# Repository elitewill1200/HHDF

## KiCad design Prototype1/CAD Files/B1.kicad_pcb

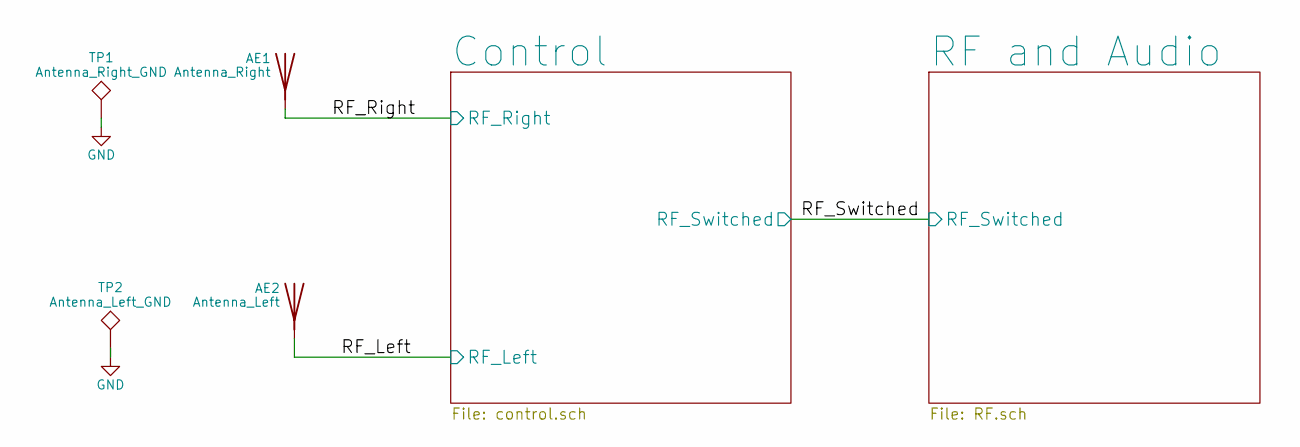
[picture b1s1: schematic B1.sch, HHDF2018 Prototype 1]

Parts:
AE1: Antenna_Right; MountingHole_5mm_Pad
AE2: Antenna_Left; MountingHole_5mm_Pad
TP1: Antenna_Right_GND; MountingHole_5mm_Pad
TP2: Antenna_Left_GND; MountingHole_5mm_Pad

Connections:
/RF_Left: AE2.1; also elsewhere on the board
/RF_Right: AE1.1; also elsewhere on the board
GND: TP1.1, TP2.1; also elsewhere on the board

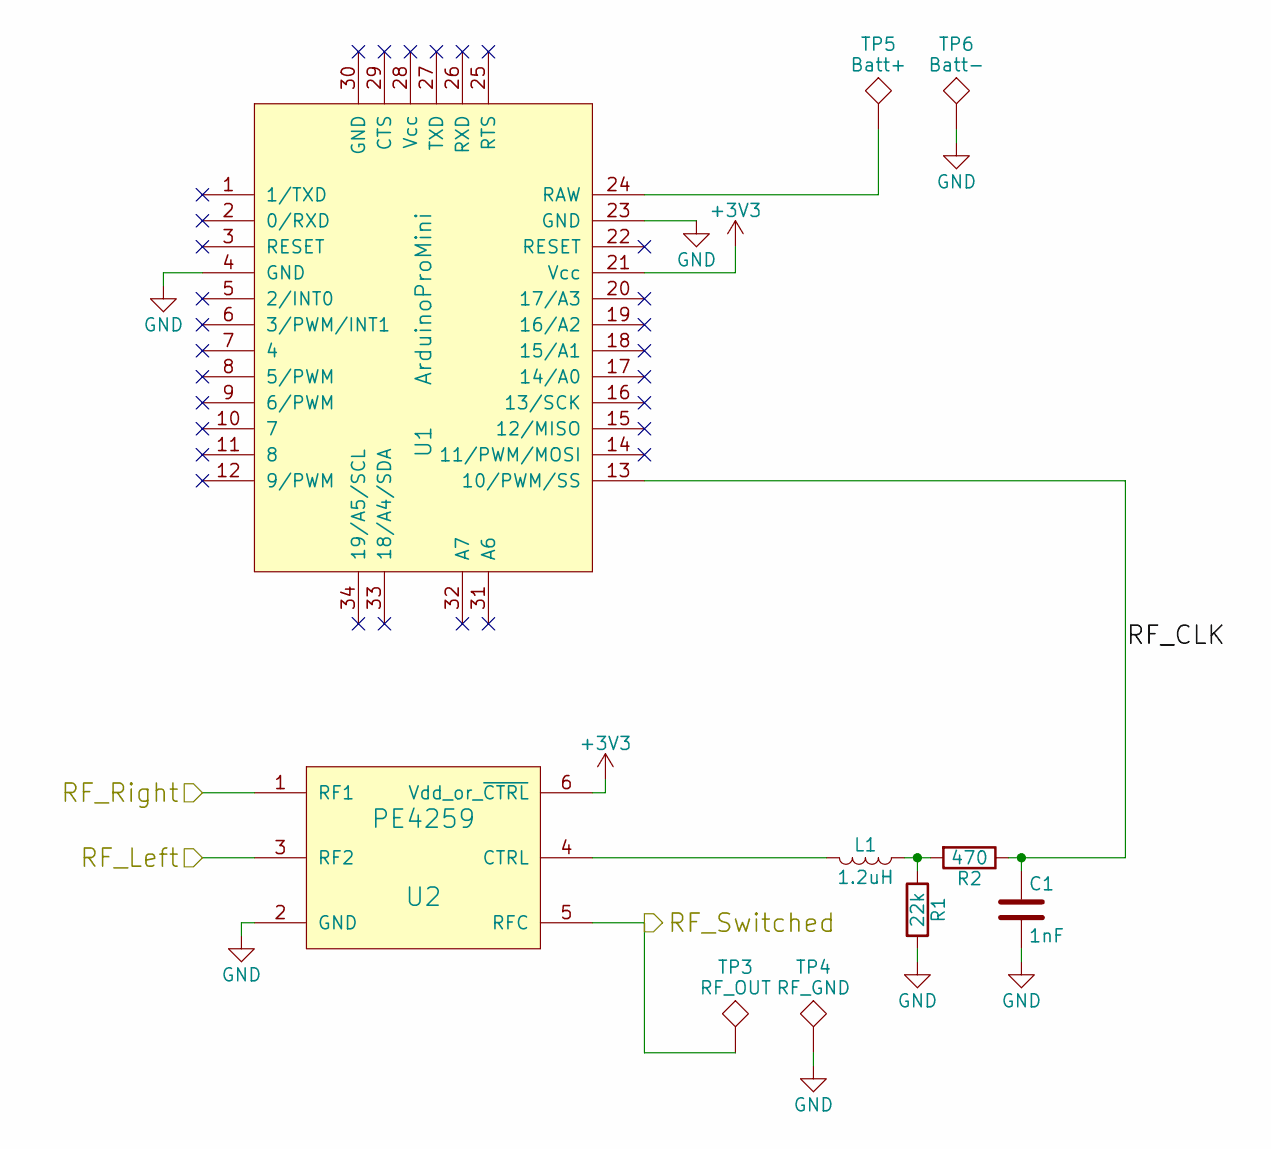
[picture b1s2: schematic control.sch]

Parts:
C1: 1nF; C_0603_HandSoldering
L1: 1.2uH; L_0603_HandSoldering
R1: 22k; C_0603_HandSoldering
R2: 470; R_0603_HandSoldering
TP3: RF_OUT; MountingHole_5mm_Pad
TP4: RF_GND; MountingHole_5mm_Pad
TP5: Batt+; SolderWirePad_single_1-5mmDrill
TP6: Batt-; SolderWirePad_single_1-5mmDrill
U1: ArduinoProMini
U2: PE4259

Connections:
+3V3: U1.21 (Vcc), U2.6 (Vdd_or_~CTRL); also elsewhere on the board
/Control/RF_CLK: C1.1, R2.1, U1.13 (10/PWM/SS)
/RF_Left: U2.3 (RF2); also elsewhere on the board
/RF_Right: U2.1 (RF1); also elsewhere on the board
/RF_Switched: TP3.1, U2.5 (RFC); also elsewhere on the board
GND: C1.2, R1.2, TP4.1, TP6.1, U1.4 (GND), U1.23 (GND), U2.2 (GND); also elsewhere on the board
unnamed: L1.1, R1.1, R2.2
unnamed: L1.2, U2.4 (CTRL)
unnamed: TP5.1, U1.24 (RAW)

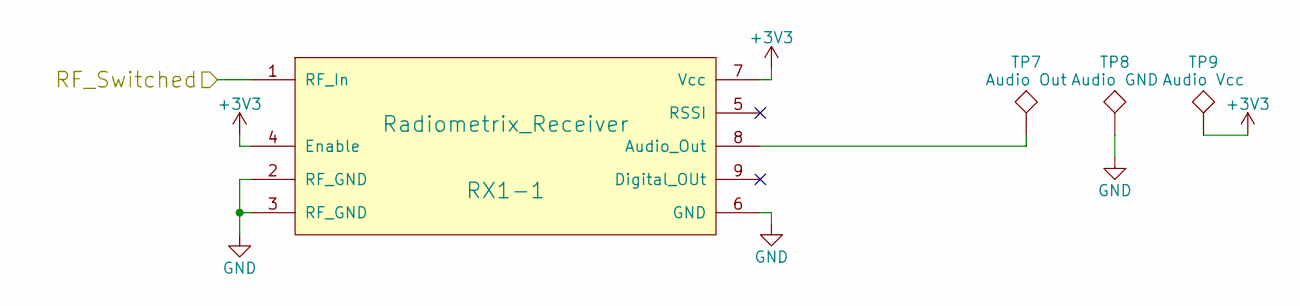
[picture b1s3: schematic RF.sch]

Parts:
RX1-1: Radiometrix_Receiver; Radiometrix_Through
TP7: Audio Out; SolderWirePad_single_1-5mmDrill
TP8: Audio GND; SolderWirePad_single_1-5mmDrill
TP9: Audio Vcc; SolderWirePad_single_1-5mmDrill

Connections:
+3V3: RX1-1.4 (Enable), RX1-1.7 (Vcc), TP9.1; also elsewhere on the board
/RF_Switched: RX1-1.1 (RF_In); also elsewhere on the board
GND: RX1-1.2 (RF_GND), RX1-1.3 (RF_GND), RX1-1.6 (GND), TP8.1; also elsewhere on the board
unnamed: RX1-1.8 (Audio_Out), TP7.1

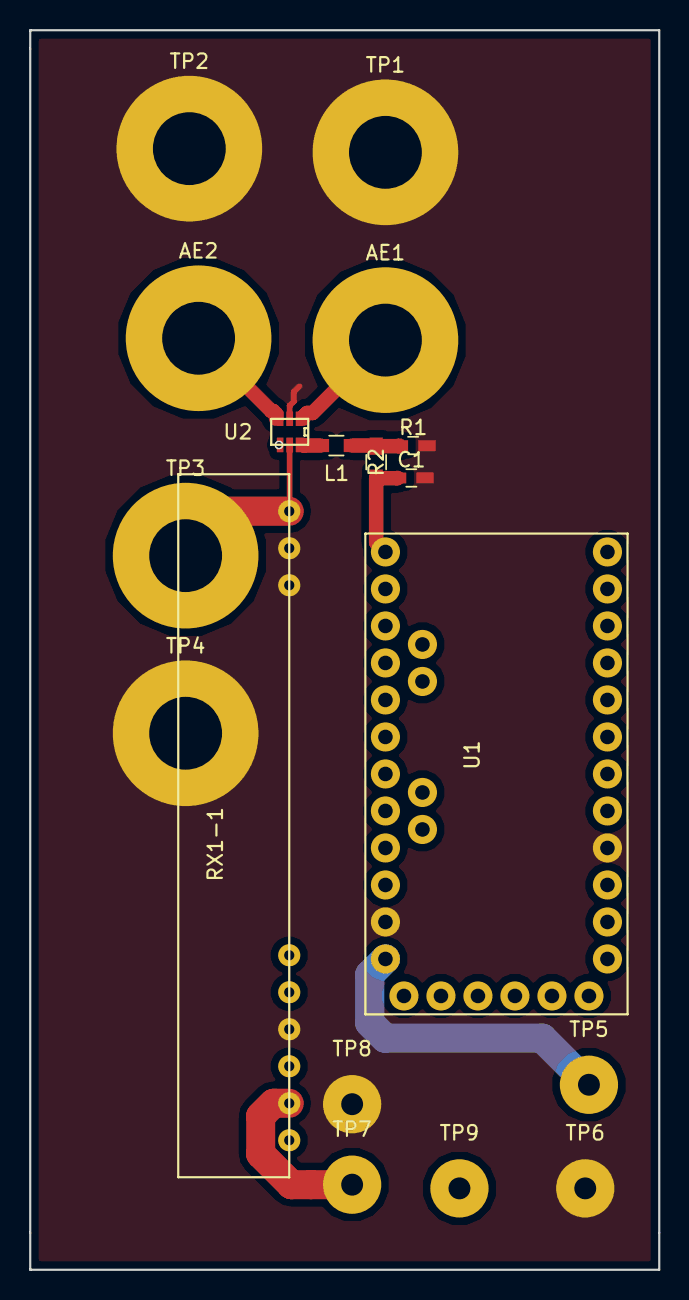
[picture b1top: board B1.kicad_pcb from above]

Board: 2 copper layers, 43.2 x 85.1 mm, 18 parts (0 on the bottom side), 10 nets.

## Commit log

2018-06-11 Added start of first protoype
2018-06-11 Added Stuff
